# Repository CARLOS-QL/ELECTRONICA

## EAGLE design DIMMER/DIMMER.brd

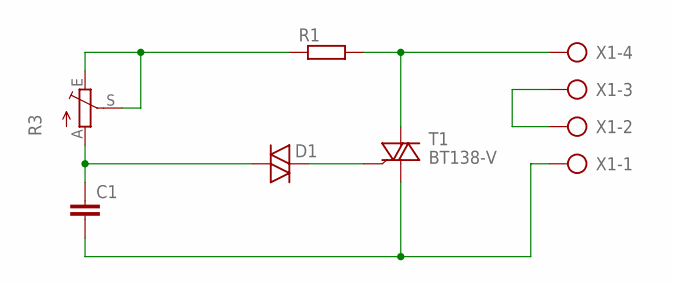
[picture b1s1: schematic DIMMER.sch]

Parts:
C1: C15/5; C15B5
D1: DIAC-GT32; GT32
R1: R-EU_0207/10; 0207/10
R3: TRIM_EU-CIP20C-4MM; CIP20C-4MM
T1: BT138-V; TO220BV
X1: AK500/4

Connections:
unnamed: D1.2, T1.G
unnamed: R1.2, T1.T2 (A2), X1.4
unnamed: X1.2, X1.3
unnamed: C1.2, T1.T1 (A1), X1.1
unnamed: C1.1, D1.1, R3.A
unnamed: R1.1, R3.E, R3.S

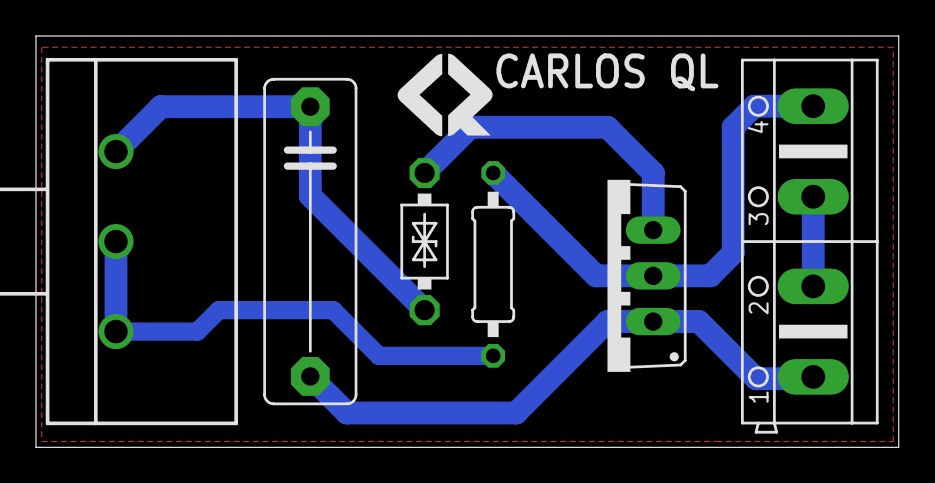
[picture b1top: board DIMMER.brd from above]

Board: 2 copper layers, 47.9 x 22.9 mm, 6 parts (0 on the bottom side), 6 nets.
